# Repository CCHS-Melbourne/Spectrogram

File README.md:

<a href="https://www.zodiaccurios.com.au/shop/p/spectrogram-mini">

# Spectrogram

It's a 36 LED stack of neopixels joy with an integrated microphone, running MicroPython:

* Audio reactive LEDs
* Acrylic-ready, to show off your creative animations
* Stepped structure to elimate gaps between edge-lit panels
* Touch-enabled to switch between all its range of features

### Building

To build the firmware it helps to use `mpbuild` like so, since this hardware will not work without `ulab`:

```
$ git clone https://github.com/mattytrentini/mpbuild && cd mpbuild
$ git clone https://github.com/v923z/micropython-ulab ulab
$ python3 -mvenv .venv && source .venv/bin/activate && pip install -e .
(.venv)$ mpbuild build ESP32_GENERIC_S3 FLASH_4M USER_C_MODULES=$PWD/ulab/code/micropython.cmake all
```

The resulting object you want to flash with the `esptool.py` command from the previous section is typically named `firmware.bin`.

### Running

```sh
cd software/micropython
./run.sh
```

### Closeup

Uoooohhh

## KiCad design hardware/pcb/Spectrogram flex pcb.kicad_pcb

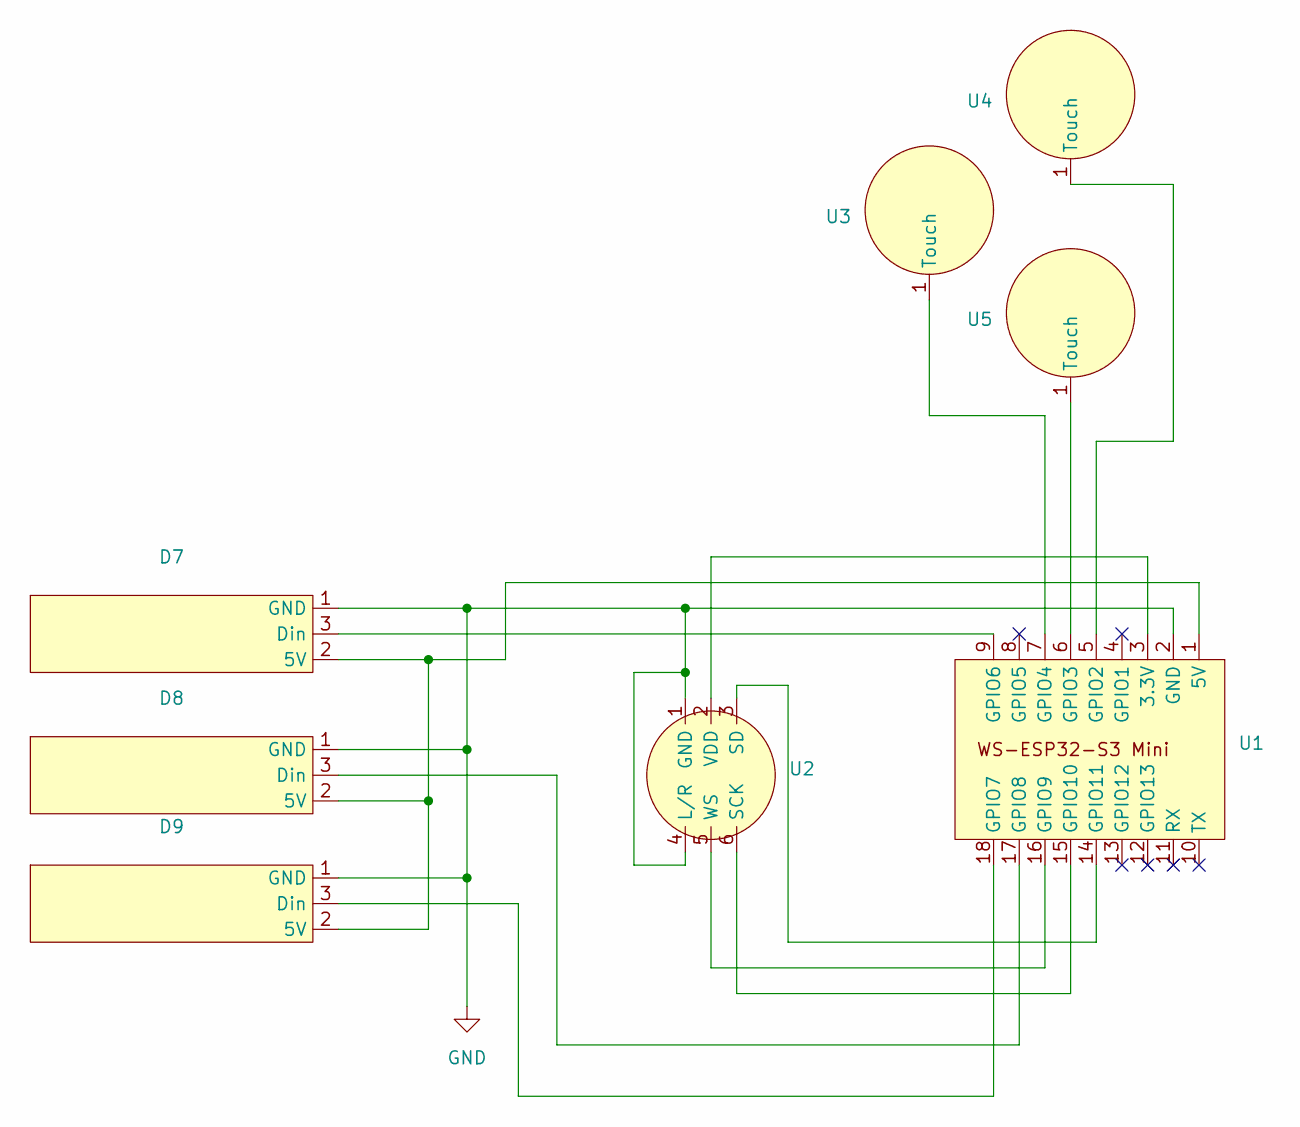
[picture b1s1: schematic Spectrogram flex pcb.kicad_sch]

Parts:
D7, D8, D9: LED strip ghost
U1: WS-ESP32-S3-Mini
U2: INMP441
U3, U4, U5: Cap touch sensor

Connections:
GND: D7.1 (GND), D8.1 (GND), D9.1 (GND), U1.2 (GND), U2.1 (GND), U2.4 (L/R)
unnamed: D7.2 (5V), D8.2 (5V), D9.2 (5V), U1.1 (5V)
unnamed: D7.3 (Din), U1.9 (GPIO6)
unnamed: D8.3 (Din), U1.17 (GPIO8)
unnamed: D9.3 (Din), U1.18 (GPIO7)
unnamed: U1.3 (3.3V), U2.2 (VDD)
unnamed: U1.5 (GPIO2), U4.1 (Touch)
unnamed: U1.6 (GPIO3), U5.1 (Touch)
unnamed: U1.7 (GPIO4), U3.1 (Touch)
unnamed: U1.16 (GPIO9), U2.5 (WS)
unnamed: U1.15 (GPIO10), U2.6 (SCK)
unnamed: U1.14 (GPIO11), U2.3 (SD)

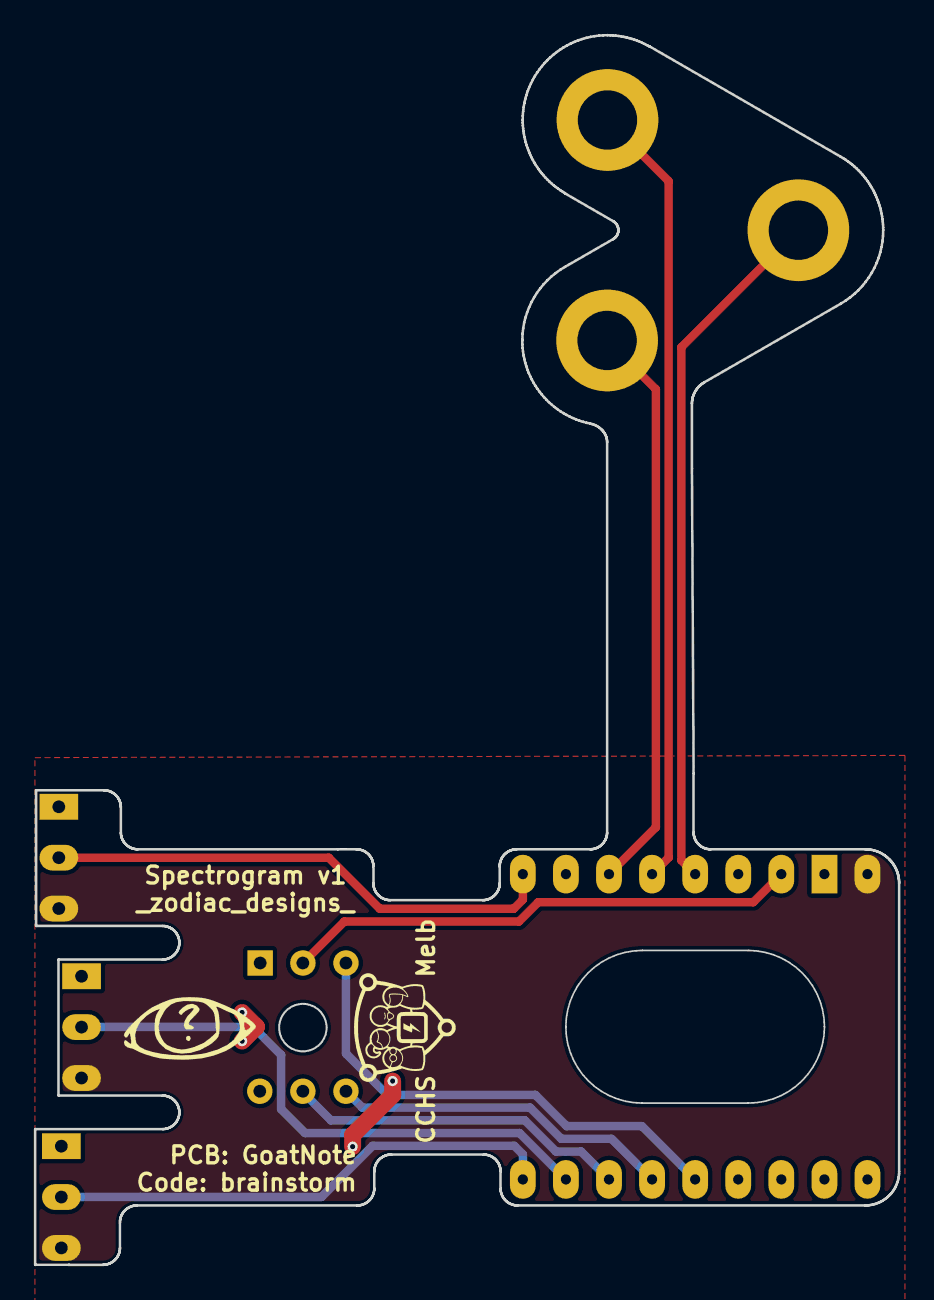
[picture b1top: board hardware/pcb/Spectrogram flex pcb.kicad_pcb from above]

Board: 2 copper layers, 50.9 x 72.5 mm, 8 parts (0 on the bottom side), 12 nets.

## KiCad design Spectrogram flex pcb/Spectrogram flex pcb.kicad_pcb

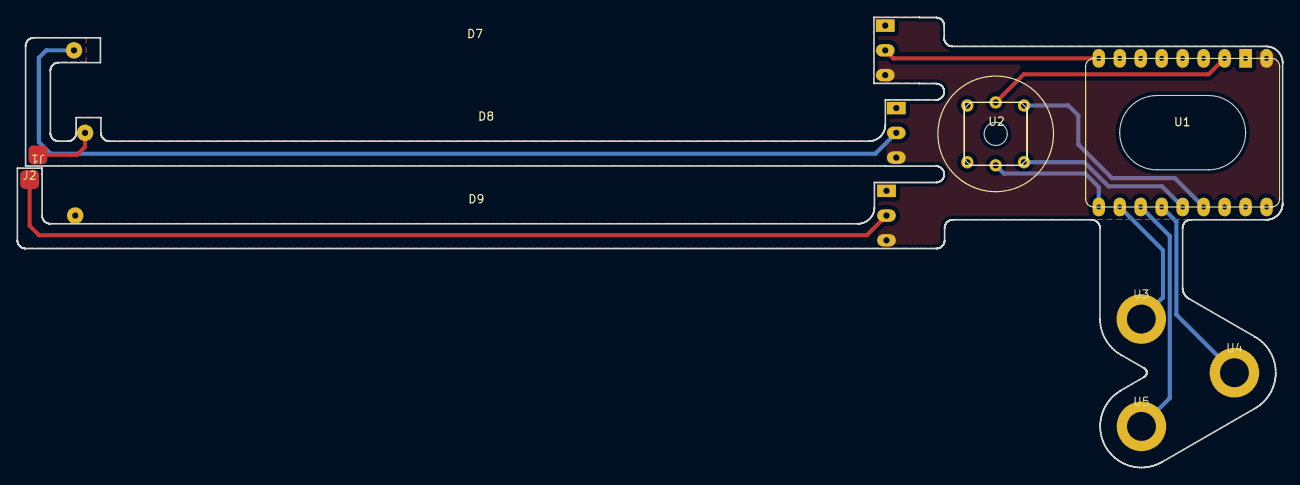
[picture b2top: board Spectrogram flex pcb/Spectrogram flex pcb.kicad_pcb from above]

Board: 2 copper layers, 153.2 x 54.5 mm, 10 parts (0 on the bottom side), 13 nets.

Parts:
D7, D8, D9: LED strip ghost
J1, J2: jumper pad
U1: WS-ESP32-S3-Mini
U2: INMP441
U3, U4, U5: Cap touch sensor

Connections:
+5V: D7.2 (5V), D8.2 (5V), D9.2 (5V), U1.1 (5V)
GND: D7.1 (GND), D8.1 (GND), D9.1 (GND), U1.2 (GND), U2.1 (GND), U2.4 (L/R)
unnamed: D7.3 (Din), U1.9 (GPIO6)
unnamed: D7.4 (Dout), D8.3 (Din)
unnamed: D8.4 (Dout), J1.1 (in)
unnamed: D9.3 (Din), J2.1 (in)
unnamed: U1.3 (3.3V), U2.2 (VDD)
unnamed: U1.18 (GPIO7), U2.5 (WS)
unnamed: U1.17 (GPIO8), U3.1 (Touch)
unnamed: U1.16 (GPIO9), U5.1 (Touch)
unnamed: U1.15 (GPIO10), U4.1 (Touch)
unnamed: U1.14 (GPIO11), U2.6 (SCK)
unnamed: U1.13 (GPIO12), U2.3 (SD)

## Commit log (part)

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2023-10-11 :dawn:
2024-03-16 Add pcb files, basic micropython led script and i2s examples repo from https://github.com/miketeachman/micropython-i2s-examples
2024-03-16 Remove some of the Rust things... for now
2024-03-16 We have not decided on licensing yet
2024-03-16 Add i2s example to refactor
2024-03-16 renamed file cause Roman said.
2024-03-16 Showing conflicts to Hank
2024-03-16 conflict resolution example
2024-03-16 Trim it down
2024-03-16 Further trimming, rename the async tasks according to objectives... correct-ish pin mapping?
2024-03-16 modified pins to correct pins with Roman's help
2024-03-26 Porting embassy_i2s example and adding in raw bytes serial output, as pointed in https://github.com/esp-rs/esp-println/issues/29#issuecomment-2016969894
2024-03-28 Remove licenses
2024-03-28 Swap nightly for task-arena-size-8192
2024-03-28 Added async uart, need to orchestrate the buffers since it goes 'task arena is full'
2024-03-28 General cleanup, comments and rearrangements, outputs mic data but cannot interpret it yet still...
2024-03-29 Ignore lock for now
2024-03-29 Test out esp-hal from HEAD and cleanup redundant variables, revert data16channel16 format
2024-04-15 micropython working example under mocleiri_2sec.py
2024-04-20 I2S_spectrogram2.py looks empty, no need to keep around?
2024-04-20 Migrate from esp32c6 to esp32s3 dev board
2024-05-11 Keep up with upstream esp-hal changes
2024-05-22 Fix thanks to https://github.com/esp-rs/esp-hal/discussions/1565#discussioncomment-9505113
2024-05-22 Back to working
2024-05-25 Still not working, spectogram is digital on the Rust code... validated that microphone connection is fine with an Arduino WebSockets example...
2024-05-29 Add attempts to reproduce https://github.com/esp-rs/esp-hal/discussions/1596
2024-06-01 Finally works with embassy/async. Need to debug byte shifting issues, but probably it's time to transition to network packets anyway so no more serial port :)
2024-06-03 Modularising this thing...
2024-06-10 Ok, so SmartLed needs to support ::new_async or similar, this will need to go deeper in the rabbit hole...
2024-06-15 Migrate to 0.18.0 esp-hal, changes in embassy packages and uart0 split() is gone. Focusing on SmartLeds + RMT async stuff
2024-06-25 Neat esp32s3 SIMD assembly resource
2024-06-30 Patched smartled for async (and its traits)... need to figure out how to work out the generic task arguments (https://github.com/embassy-rs/embassy/issues/1837) /cc @jubeormk1
2024-07-14 A bit more interesting patterns with randint
2024-07-14 Testing ulab's fft spectrogram method... why is everyone else using goertzel algorithm?... something broke, leds are not flashing on boot/main.py now
2024-07-14 Forgot to await the create_task, of course, back to work on fft...
2024-07-15 Getting I2S init errors:
    #>>> m = mic.Mic()
    #E (37838) i2s_common: i2s_new_channel(867): there should be at least 2 DMA buffers
    #E (37848) i2s_std: i2s_channel_init_std_mode(204): input parameter 'handle' is NULL
    #E (37848) i2s_common: i2s_channel_register_event_callback(316): input parameter 'handle' is NULL
    #E (37858) i2s_common: i2s_channel_enable(1077): input parameter 'handle' is NULL
    I suspect that's ESP-IDF from main (HEAD) since they seem to start moving I2S to a separate compenent/driver that might require DMA arguments.
2024-07-15 Getting data from the Mic, just have to be careful about rawsamples buffer sizing and the first 1024 bytes .readinto() from the microphone handler
2024-07-16 Led lighting show with channel
2024-07-21 hsv2rgb experiments, returning wrong values for now :/
2024-07-21 Testing brightness control, some unexpected blue color glitches, perhaps due to slow modulo/division timing?
2024-07-23 Looks reactive now thanks to @GoatNote :)
2024-07-23 Cleanup
2024-07-24 Open PCB files with KiCad 8.0.0
2024-07-24 Adjust for actual edgelit board
2024-07-24 Quite a bit of numerical tweaking and optimizations pending here... all leds enabled though
2024-07-26 Profiling... with 36 leds there's an average of nearly 200ms response time, unacceptable
2024-07-28 Add touch, concurrent tasks with asyncio.gather()
2024-07-28 Add @GoatNote color palette code to edgelit-specific branch
2024-08-03 Correct indentation, change mic pins because the ones of the board lifted... hot glued it now to oblivion, so shouldn't happen again
2024-08-04 Shaved off ~100ms, need to put back all the fft_ranges though since I changed SAMPLE_RATE and SAMPLE_COUNT to get closer to chatbot default sampling across the industry/APIs
2024-08-04 Back to all leds, adjusted sample size, we need to discuss led allocation and the need for sum_and_scale
2024-08-04 Use numpy as much as possible instead of enumerating the generator
2024-08-04 Annotate some profiling results close to the related code
2024-08-10 pushed through led colour map, refactored fft sum scale, binned octaves in fft
2024-08-10 Changed ranges for 1/2 octave per led
2024-08-11 made ambient noise not scale to max brightness
    The previous intensity scaling code made the lowest ambient noise the brightest colour (bad), then when a loud tone played the noise floor dropped (desirable). Interpolating across a range means that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
2024-08-11 Automated picking of FFT ranges to one octave per led
    in init, calculate the tones resulting of the fft, with respect to the microphone parameters. Calculate the borders of the frequencies with respect to octaves of A. Use the frequencies to check at wh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
2024-08-11 added colour mapping to note space
    Added modes: intensity and synethesia, where notes are colours. Best to play piano or organ music to watch the second mode.
2024-08-19 Adding SVG of circuit board refactor
    as above
2024-08-20 Add new prototype outline to a more fitting location
2024-08-20 Old zones don't seem to be removable, will edit the text file next, wish me luck
2024-08-20 Successful removal of stray zones (manually)
2024-08-20 Imported SMD microphone, a bunch of footprints are missing (Pancake library)
2024-08-20 Change custom testpoints for those present in the default KiCad library
2024-08-28 Add inmp441 mic part for the PCB
2024-08-28 playing around with LED UX
2024-08-29 Changed tone borders, bad attempt at ring buffer
    Made tone borders start halfway between notes, instead of directly on them
2024-09-01 Big cleanup, don't panic @GoatNote
2024-09-01 Barebones description of what this thing does
2024-09-01 Refer to some Rust interesting no_std FFT source
2024-09-04 Switch to non-blocking I/O, as suggested by Angus
2024-09-04 Cleanup commented code and stray spaces/tabs
2024-09-07 Oops, that variable was actually needed
2024-09-07 @projectgus, not sure I'm doing the non_blocking right?:
    ```python
    while True:
    t0 = ticks_us()
    # Use non-blocking instead of streaming mode since we are in a loop!
    num_read = self.microphone.readinto(rawsamples)
    samples = np.frombuffer(rawsamples, dtype=np.int16)
2024-09-08 Thanks @projectgus, very nice speedup!:
    mic sampling: 0 ms
    wled function: 39 ms
    synesthesia : 3 ms
    mic sampling: 1 ms
    wled function: 45 ms
    synesthesia : 2 ms
2024-09-22 Rename file for neatness
2024-09-22 brightness scaling and unfinished ring buffer added
2024-09-22 adding pin defs back in, whoops
2024-09-26 added 'waterfall' or time series mode
    Forgive the -1 and -2 indexing throughout, please.
    Please note that my board now has different pins to yours @brainstorm
2024-10-13 added db scaling to values, now bass is not dominating display
2024-10-22 Push
2024-10-25 Add ulab+micropython firmware for "Generic" ESP32 and ESP32S3. With latest versions of ulab, micropython, esp-idf and micropython-lib... built with micropython-builder (instead of mpbuild).
    Also the Lolin S3 dev board, which is currently unsupported by micropython upstream (unmerged PR): https://github.com/micropython/micropython/pull/9177
    Firmware images are compiled against ESP-IDF 5.4 series, which require a few tweaks at this point in time: https://github.com/micropython/micropython/issues/15287#issuecomment-2211668377
    The only downsides are some NimBLE security-related data structure and also PPP-related code fixes... neither of which we'll use for now, I reckon.
    Hope those firmware
2024-10-25 Move standalone tests elsewhere
2024-10-25 Both asyncio.gather and asyncio.create_task should spawn async tasks and execute them well... instead, I'm finding that when enabling the microphone task, touch does not print(rv) anymore :/
2024-10-25 Just Mic and one touch button
2024-10-25 Try another rearrangement when spawning async tasks: first we spawn the 3 touch buttons and then mic... mic task only seems to work when it's the only task spawned (when no touch tasks are spawned)..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
2024-10-25 Offer minimal guidance to flash this thing on a dev board
2024-10-31 Updating the svgs for the flex PCB outline and acrylic
2024-11-04 touch: Await for the dirty sensor workaround.
2024-11-12 Implement ThreadFlag as suggested in https://github.com/CCHS-Melbourne/PancakeLEDs/pull/1#issuecomment-2467146890
2024-11-13 Do not await the flag.wait(). Only one iteration of print(id(self), rv) is shown though:
    % mpremote mount .
    Local directory . is mounted at /remote
    Connected to MicroPython at /dev/cu.usbmodem1101
    Use Ctrl-] or Ctrl-x to exit this shell
    >
    MicroPython v1.25.0-preview.22.gfb6c8da on 2024-11-11; Generic ESP32S3 module with ESP32S3
2024-11-16 [doc] Improve docs on how to flash and build custom ulab firmware
2024-11-16 Updating with my flex PCB design work
2024-11-17 Updating Flex PCB
2024-11-17 Uploading/backing up edge cut svg
2024-11-18 Figuring out why the asyncio tasks block when they shouldn't... now mic intervals are 1 second apart, too much latency
2024-11-19 WIP: Remove some copying and allocations
    By making a 'bytearray' that points into our samples array, and then
    taking a memoryview of this and slicing it, we can copy directly
    from the I2S DMA buffer into our 'samples' array.
2024-11-19 Add easy way to run this for debugging purposes
2024-11-19 Focus on profiliing instead of debug messages...
2024-11-30 Drafting menu thing...
2024-11-30 Add the nonworking code to work on the other machine...
2025-02-27 Big cleanup and re-org, let's publish this thing :D
2025-02-27 Remove prebuilt images for now, moved loose files not related to firmware under utils, pending deletion and/or re-structuring
2025-02-27 Add @goatnote 3d printed feet
2025-02-27 Remove .vscode cruft
2025-02-27 Modern equalizer, thanks @GoatNote for the naming
2025-03-25 Added control for the highest decibels level
2025-03-25 More navigation for the decibel control
2025-03-26 Added AGC, reduced spammy outputs
2025-03-30 Found reason for laggy interface and set 15fps
    The mic did not have a yielding asyncio.await(whatever). Added back in timers and aimed for a 15fps.
2025-03-31 Made menu less overshoot prone, misc crashes, simplified brightness
    Also made the pan mode have the blue colour scheme
2025-03-31 Made menu position persist between main modes
2025-04-02 Change name back as suggested by @GoatNote
2025-04-02 Add Tindie badge on repo
2025-04-02 Move badge higher
2025-04-06 Added basic relocation with resolution changes
2025-07-26 PCB revision
2025-07-26 Uptting up code in current working menu
2025-09-27 touch ups to work with revised flex pcb and file structure
2025-10-03 first pass at fixing up synesthesia mode
2025-10-14 Watchdog added, hues overhauled
    per JO's quip: "Is is a point where you go: hmm, version control is something I should have done more of?"
2025-10-14 Simplifying menuing and adding brightness subsubmodes
2025-10-18 Rearranged Menu and some hues
2025-10-19 Full sync
2025-11-02 DB scaling better and status led turns off
2025-11-02 deleted file dup
2025-11-04 Fixed pan crash, made menu behavior more consistent
2025-11-17 Config approach adopted, menu scaled for little spectro
2026-02-19 First cut of determiner
    It picks up notes and keys, but I have a pretty silly mistake decaying the aggregator bin each note each octave, so doing version control then checking that.
2026-02-19 Update fp-info-cache
2026-02-20 second cut of key determiner
    Version control before building a chord tracker and pivoting to operating on the amplitude of the closest FFT tone, instead of max(bin)
